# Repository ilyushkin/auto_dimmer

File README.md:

# Dimmer with Automatic Countdown for IKEA NYMANE Lamp
Automatic dimmer for the IKEA NYMANE lamp using the low-cost 8-bit AVR ATtiny13A microcontroller.

If the button is held for more than 2 seconds, auto-dimming mode activates with a 20-minute countdown,
during which the lamp gradually dims from the current brightness to zero.
This is convenient for falling asleep without leaving the light on.
The logic is somewhat similar to the dimming-out functionality of the Philips Wake-up Light alarm clock, just without all the bells and whistles.

The project is based on the AVR ATtiny13A microcontroller and written in AVR assembly. It was a fun assembly side-project that begun during the COVID-19 lockdown, and I finally decided to publish it.

The PCB is designed to fit within the base of the IKEA NYMANE swing-arm wall lamp (art. No. 103.569.62) and replace the original basic dimmer that comes with the lamp.

The lamp is turned on and off by pressing the button, unlike the original version, where you had to turn the knob to power it on.
The main advantage of this approach is that the brightness setting is not reset every time the lamp is turned off.

Brightness is adjusted by rotating the potentiometer knob.

I decided to use the RV09 potentiometer because it was the easiest way to retain the brightness level between MCU power cycles.
For this reason, I chose not to use a rotary encoder (e.g., EC11 with an integrated button), as that would require storing the actual brightness level in EEPROM.

I used a simple linear potentiometer without an embedded button, as potentiometers with built-in buttons are rather rare, plus I already had the RV09 in stock.
Since the potentiometer lacks a button, the design includes a plastic inlay that fits inside the metal cap of the original control knob to make it pushable.
This inlay allows the entire knob to slide slightly along the potentiometer shaft and press the pushbutton through a plastic spring-loaded lever mounted next to the potentiometer on the PCB.

The microcontroller is powered by an unisolated power supply based on a capacitive voltage divider, as all parts of the lamp are double insulated.

To achieve this, I designed a 3D-printed internal plastic casing and reused the screws from the lamp's original internal plastic structure.

All plastic parts are also published on Thingiverse:
https://www.thingiverse.com/thing:6785874

Since there is no galvanic isolation, _the microcontroller should only be flashed when the mains power is off_.

For safety reasons, I used a 2.54mm ISP socket instead of a header, as the header can be accidentally touched when removing the lamp from the wall while it's still energized.

## Schematics

## Photos

The original internals of the lamp: the basic DIAC-TRIAC dimmer on the left and the connector box on the right.

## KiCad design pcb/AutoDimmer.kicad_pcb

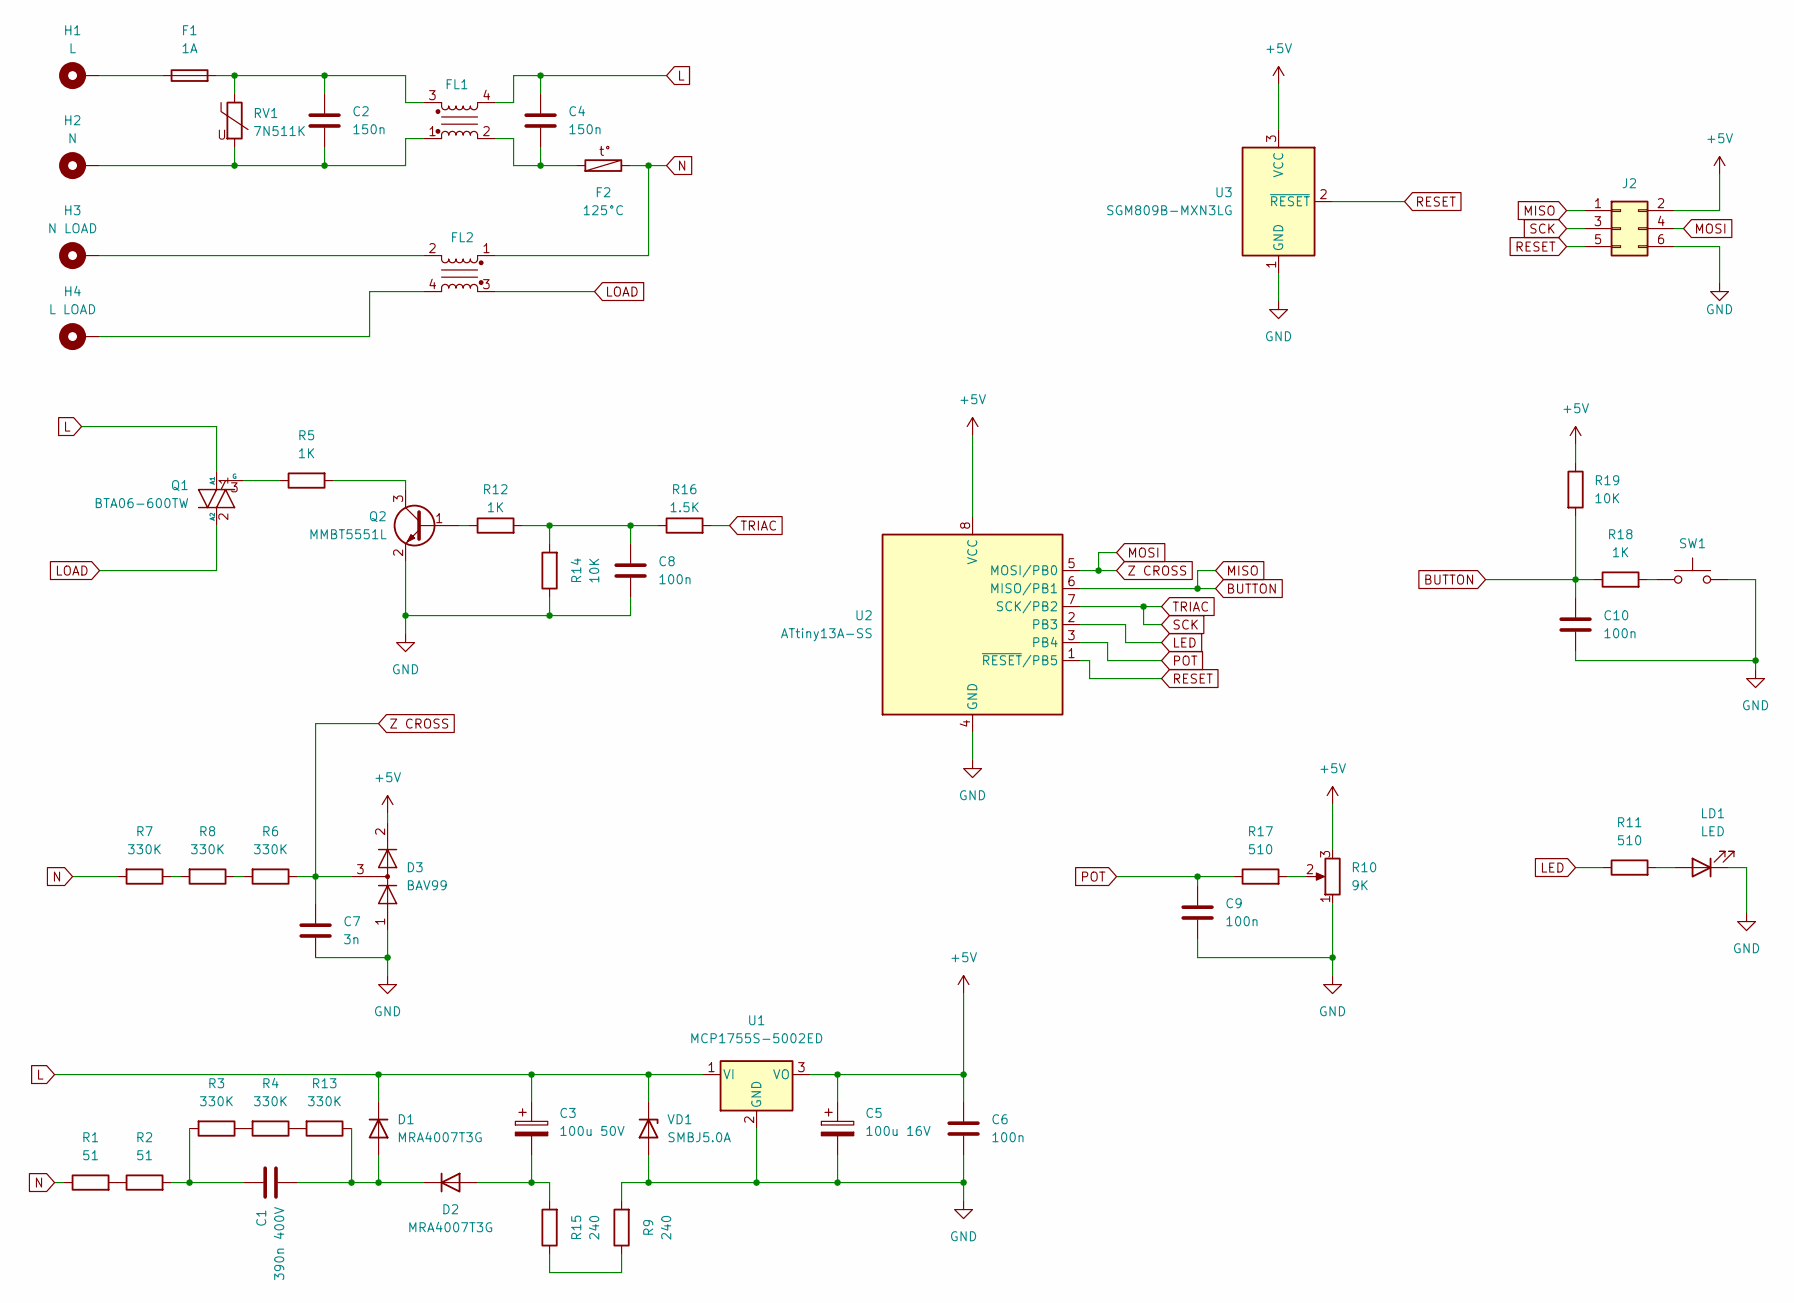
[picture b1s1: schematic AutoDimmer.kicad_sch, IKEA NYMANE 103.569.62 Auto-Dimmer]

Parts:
C1: 390n 400V; C_Rect_L18.0mm_W9.0mm_P15.00mm_FKS3_FKP3
C2, C4: 150n; C_Rect_L10.3mm_W5.0mm_P7.50mm_MKS4
C3: 100u 50V; C_Radial_D8.0mm_H11.5mm_P3.50mm
C5: 100u 16V; CP_EIA-3528-15_AVX-H_Pad1.50x2.35mm_HandSolder
C6, C8, C9, C10: 100n; C_1206_3216Metric_Pad1.33x1.80mm_HandSolder
C7: 3n; C_1206_3216Metric_Pad1.33x1.80mm_HandSolder
D1, D2: MRA4007T3G; D_SMA
D3: BAV99; SOT-23
F1: 1A; R_Axial_DIN0414_L11.9mm_D4.5mm_P15.24mm_Horizontal
F2: 125°C; C_Rect_L13.0mm_W3.0mm_P10.00mm_FKS3_FKP3_MKS4
FL1, FL2: Filter_EMI_CommonMode; L_CommonMode_Wuerth_WE-CMB-XS
H1: L; MountingHole_2.2mm_M2_Pad
H2: N; MountingHole_2.2mm_M2_Pad
H3: N LOAD; MountingHole_2.2mm_M2_Pad
H4: L LOAD; MountingHole_2.2mm_M2_Pad
J2: Conn_02x03_Odd_Even; PinSocket_2x03_P2.54mm_Vertical_SMD
LD1: LED; LED_D3.0mm
Q1: BTA06-600TW; TO-220-3_Horizontal_TabDown
Q2: MMBT5551L; SOT-23
R1, R2: 51; R_Axial_DIN0207_L6.3mm_D2.5mm_P2.54mm_Vertical
R3, R4, R6, R7, R13: 330K; R_1206_3216Metric_Pad1.30x1.75mm_HandSolder
R5, R12, R18: 1K; R_1206_3216Metric_Pad1.30x1.75mm_HandSolder
R8: 330K; R_Axial_DIN0207_L6.3mm_D2.5mm_P15.24mm_Horizontal
R9, R15: 240; R_1206_3216Metric_Pad1.30x1.75mm_HandSolder
R10: 9K; Potentiometer_Alps_RK09K_Single_Vertical
R11, R17: 510; R_1206_3216Metric_Pad1.30x1.75mm_HandSolder
R14, R19: 10K; R_1206_3216Metric_Pad1.30x1.75mm_HandSolder
R16: 1.5K; R_1206_3216Metric_Pad1.30x1.75mm_HandSolder
RV1: 7N511K; RV_Disc_D7mm_W3.9mm_P5mm
SW1: SW_Push; SW_PUSH_6mm_H5mm
U1: MCP1755S-5002ED; SOT-223-3_TabPin2
U2: ATtiny13A-SS; SOIC-8_3.9x4.9mm_P1.27mm
U3: SGM809B-MXN3LG; SOT-23
VD1: SMBJ5.0A; D_SMB

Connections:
+5V: C5.1, C6.1, D3.2 (A), J2.2, R10.3, R19.1, U1.3 (VO), U2.8 (VCC), U3.3 (VCC)
BUTTON: C10.1, J2.1, R18.1, R19.2, U2.6 (MISO/PB1)
GND: C5.2, C6.2, C7.2, C8.2, C9.2, C10.2, D3.1 (K), J2.6, LD1.1 (K), Q2.2 (E), R9.2, R10.1, R14.1, SW1.2, U1.2 (GND), U2.4 (GND), U3.1 (GND), VD1.2 (A)
L: C3.1, C4.1, D1.1 (K), FL1.4, Q1.1 (A1), U1.1 (VI), VD1.1 (K)
LED: R11.1, U2.2 (PB3)
LOAD: FL2.3, Q1.2 (A2)
MOSI: C7.1, D3.3 (K), J2.4, R6.1, U2.5 (MOSI/PB0)
N: F2.2, FL2.1, R1.1, R7.2
unnamed: C1.1, R2.2, R3.2
unnamed: C2.1, F1.2, FL1.3, RV1.1
unnamed: C2.2, FL1.1, H2.1, RV1.2
unnamed: C4.2, F2.1, FL1.2
unnamed: C8.1, R12.2, R14.2, R16.1
unnamed: C1.2, D1.2 (A), D2.1 (K), R13.1
unnamed: C3.2, D2.2 (A), R15.2
unnamed: F1.1, H1.1
unnamed: FL2.2, H3.1
unnamed: FL2.4, H4.1
unnamed: LD1.2 (A), R11.2
unnamed: Q1.3 (G), R5.1
unnamed: Q2.1 (B), R12.1
unnamed: Q2.3 (C), R5.2
unnamed: R1.2, R2.1
unnamed: R3.1, R4.2
unnamed: R6.2, R8.1
unnamed: R7.1, R8.2
unnamed: R10.2, R17.2
unnamed: R4.1, R13.2
unnamed: R9.1, R15.1
unnamed: R18.2, SW1.1
POT: C9.1, R17.1, U2.3 (PB4)
RESET: J2.5, U2.1 (~RESET/PB5), U3.2 (~RESET)
SCK: J2.3, R16.2, U2.7 (SCK/PB2)

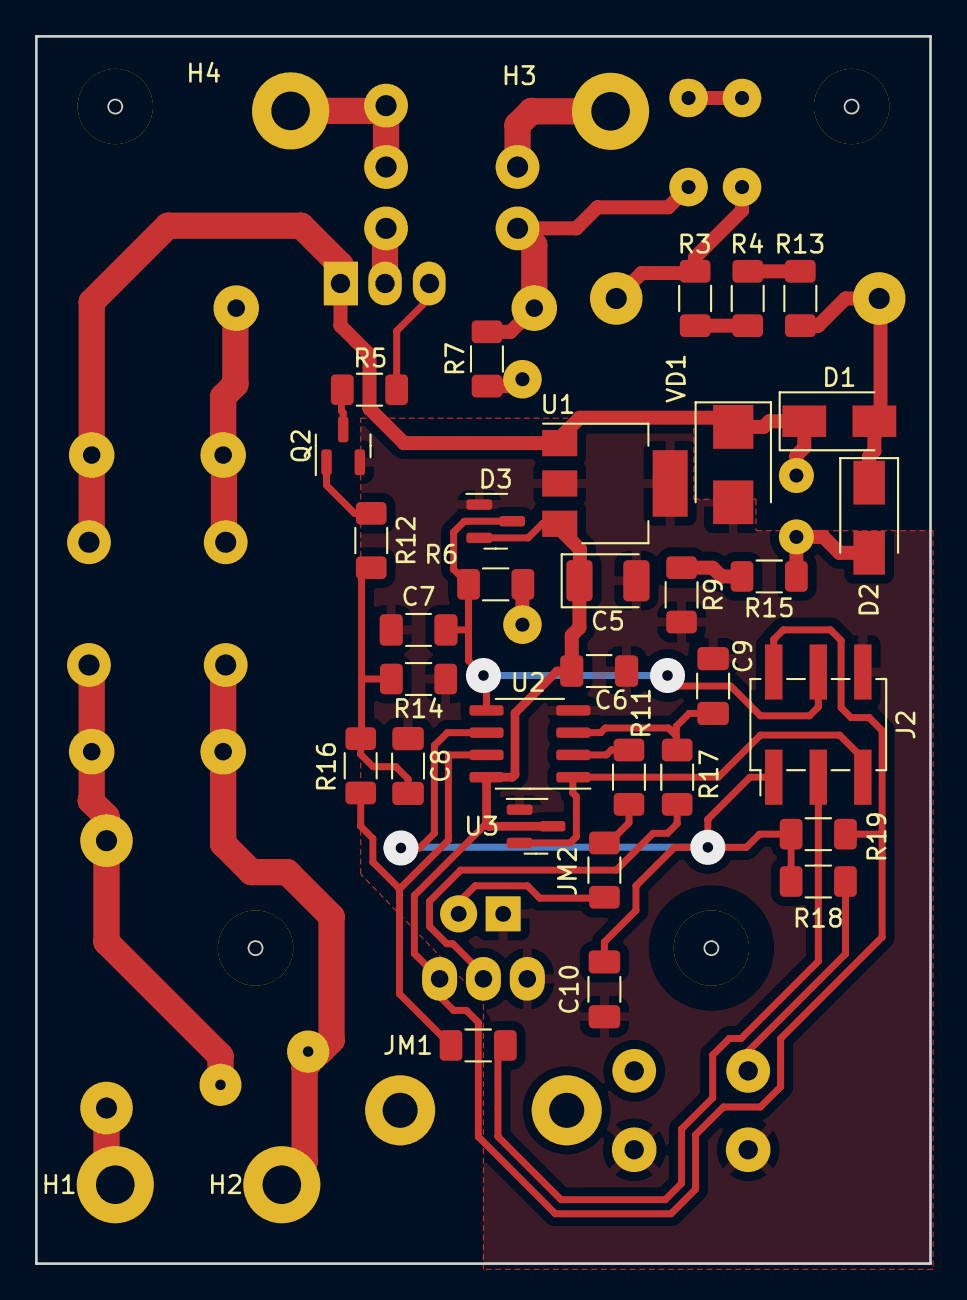
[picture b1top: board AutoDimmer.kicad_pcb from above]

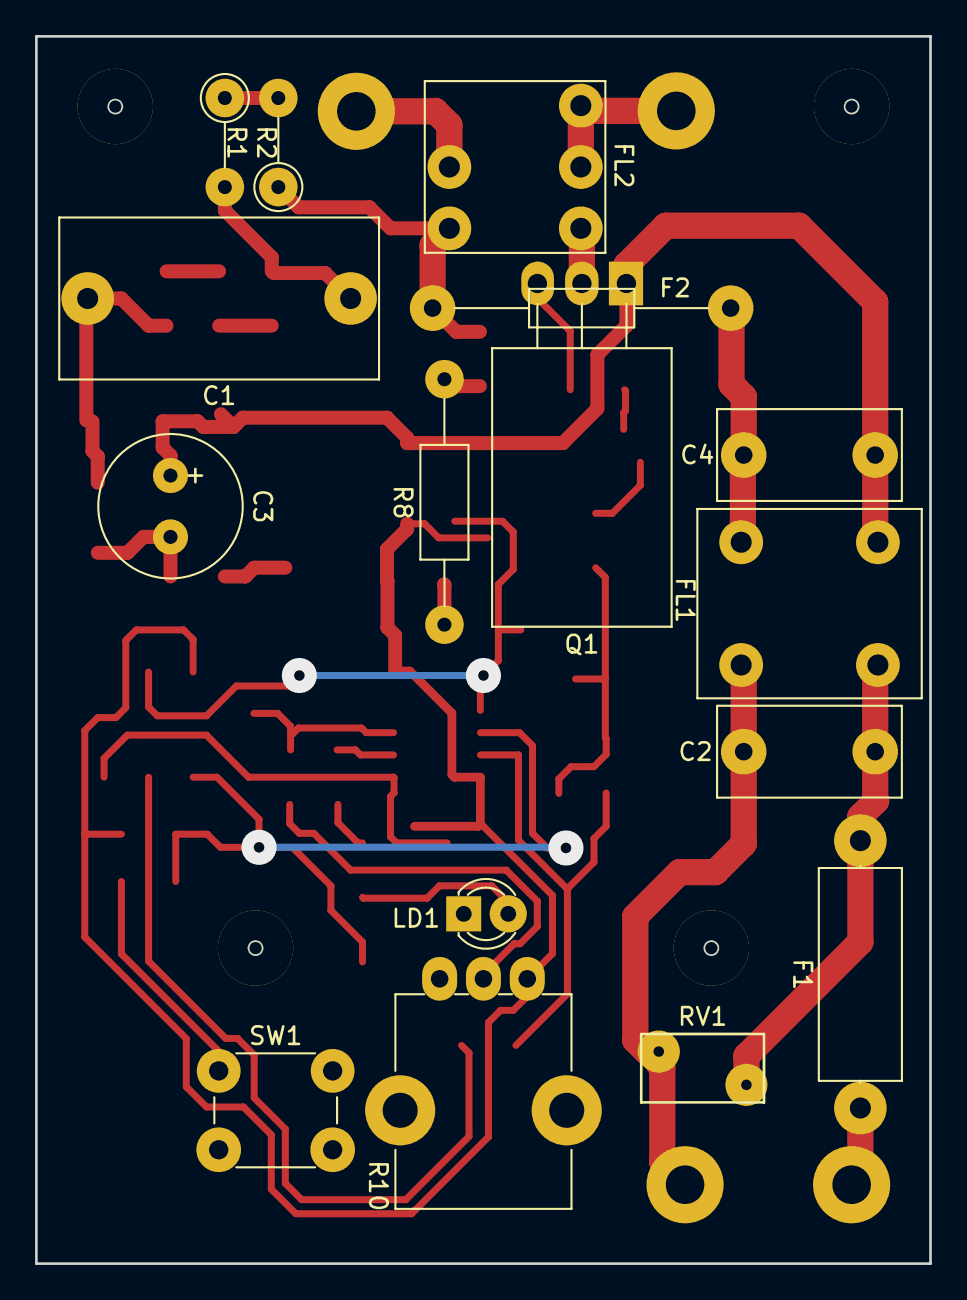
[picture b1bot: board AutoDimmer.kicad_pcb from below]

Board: 2 copper layers, 51.0 x 70.0 mm, 52 parts (16 on the bottom side), 35 nets.

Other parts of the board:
JM1, JM2: R_1206_3216Metric_Pad1.30x1.75mm_HandSolder

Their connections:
unnamed: JM2.1, JM2.2
TRIAC: JM1.1, JM1.2

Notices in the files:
pcb/AutoDimmer.kicad_sch:
Copyright Alexey S. Ilyushkin
